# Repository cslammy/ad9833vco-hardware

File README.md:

# ad9833vco-hardware
Schematics, eagle files etc for AD9833 VCO

I have an ongoing project--building a volt octave VCO using the AD9833 function generator IC.  This repo has current zips of Eagle files, BOMs, gerbers, and PDFs of boards and schematics.

What I post here (1-30-23) works on my bench but could stand some improvement in terms of frequency stability and generally improving the triangle to ramp conversion. The rest of it seems to work. I will update the zips here as I continue to improve this design...

Blog post (which links other posts about this project) is here.
https://audiodiwhy.blogspot.com/2023/01/ad9833-audio-vco-works-work-in-progress.html

Embedded C for this project can be found in this repo: AD9833-VCO

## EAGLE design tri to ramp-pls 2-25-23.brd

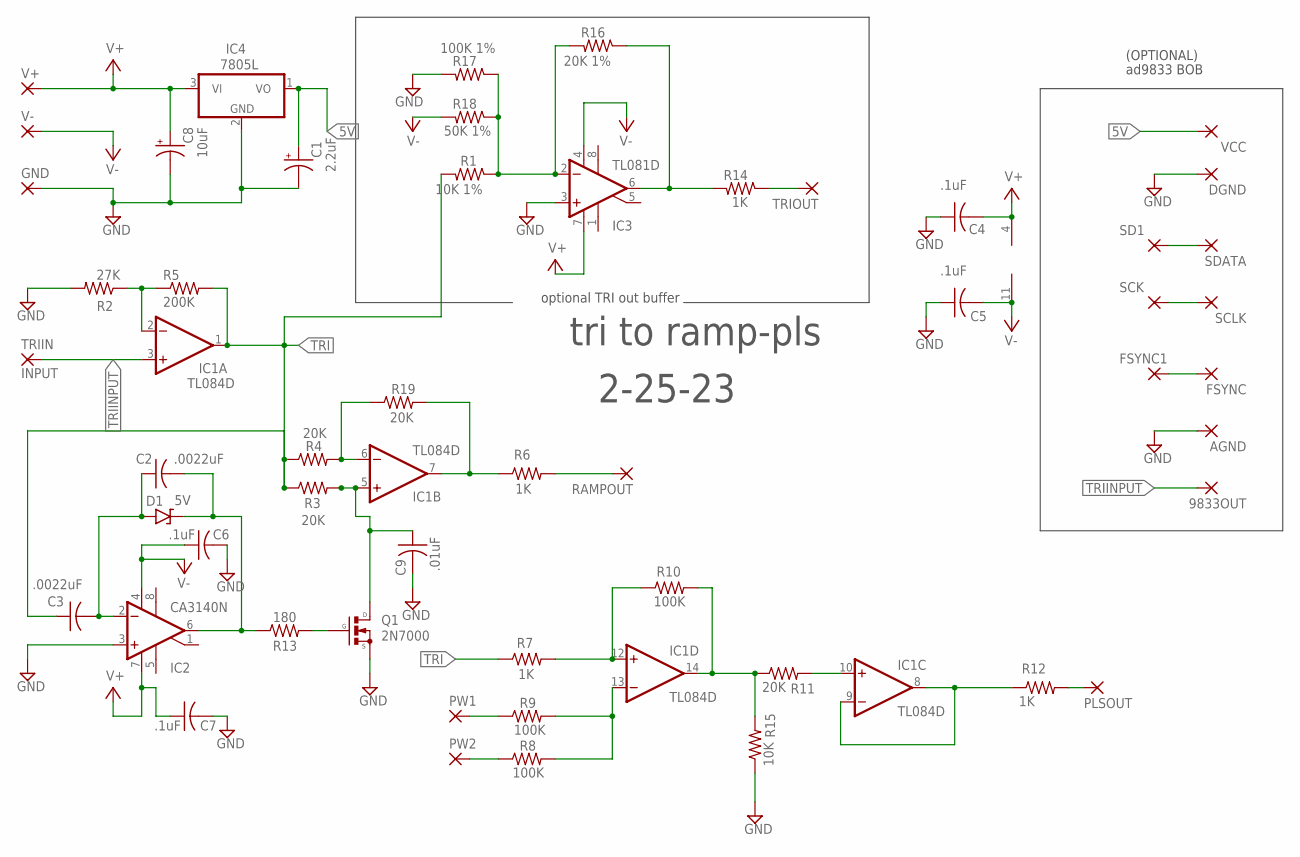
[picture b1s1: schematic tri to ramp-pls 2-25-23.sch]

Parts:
9833OUT: WIREPAD1,6/0,8; 1,6/0,8
AGND: WIREPAD1,6/0,8; 1,6/0,8
C1: 2.2uF; E5-4
C2: .0022uF; C050-030X075
C3: .0022uF; C050-035X075
C4, C5, C6, C7: .1uF; C025-025X050
C8: 10uF; E5-4
C9: .01uF; C050-035X075
D1: 5V; DO41-3
DGND: WIREPAD1,6/0,8; 1,6/0,8
FSYNC, FSYNC1: WIREPAD1,6/0,8; 1,6/0,8
GND: WIREPAD1,6/0,8; 1,6/0,8
IC1: TL084D; SO14
IC2: CA3140N; DIL08
IC3: TL081D; SO08
IC4: 7805L; ADAFRUIT_TO92
PLSOUT: WIREPAD1,6/0,8; 1,6/0,8
PW1, PW2: WIREPAD1,6/0,8; 1,6/0,8
Q1: 2N7000; TO92-
R1: 10K 1%; 0204/7
R2: 27K; 0204/7
R3, R4, R11, R19: 20K; 0204/7
R5: 200K; 0204/7
R6, R7, R12, R14: 1K; 0204/7
R8, R9, R10: 100K; 0204/7
R13: 180; 0204/7
R15: 10K; 0204/7
R16: 20K 1%; 0204/7
R17: 100K 1%; 0204/7
R18: 50K 1%; 0204/7
RAMPOUT: WIREPAD1,6/0,8; 1,6/0,8
SCK: WIREPAD1,6/0,8; 1,6/0,8
SCLK: WIREPAD1,6/0,8; 1,6/0,8
SD1: WIREPAD1,6/0,8; 1,6/0,8
SDATA: WIREPAD1,6/0,8; 1,6/0,8
TRIIN: INPUT; 1,6/0,8
TRIOUT: WIREPAD1,6/0,8; 1,6/0,8
V+: WIREPAD1,6/0,8; 1,6/0,8
V-: WIREPAD1,6/0,8; 1,6/0,8
VCC: WIREPAD1,6/0,8; 1,6/0,8

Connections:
5V: C1.+, IC4.1 (VO), VCC.1
GND: AGND.1, C1.-, C4.1, C5.1, C6.2, C7.2, C8.-, C9.2, DGND.1, GND.1, IC2.3 (+IN), IC3.3 (+IN), IC4.2 (GND), Q1.3 (S), R2.2, R15.1, R17.2
unnamed: IC1.2 (-IN), R2.1, R5.1
unnamed: PW1.1, R9.1
unnamed: SD1.1, SDATA.1
unnamed: IC1.12 (+IN), R7.2, R10.1
unnamed: IC1.6 (-IN), R4.2, R19.1
unnamed: C9.1, IC1.5 (+IN), Q1.1 (D), R3.2
unnamed: C2.1, C3.2, D1.A, IC2.2 (-IN)
unnamed: IC1.7 (OUT), R6.1, R19.2
unnamed: C2.2, D1.C, IC2.6 (OUT), R13.1
unnamed: Q1.2 (G), R13.2
unnamed: IC1.14 (OUT), R10.2, R11.1, R15.2
unnamed: R6.2, RAMPOUT.1
unnamed: IC1.10 (+IN), R11.2
unnamed: IC1.8 (OUT), IC1.9 (-IN), R12.1
unnamed: PLSOUT.1, R12.2
unnamed: IC1.13 (-IN), R8.2, R9.2
unnamed: IC3.2 (-IN), R1.1, R16.2, R17.1, R18.1
unnamed: PW2.1, R8.1
unnamed: R14.1, TRIOUT.1
unnamed: SCK.1, SCLK.1
unnamed: FSYNC.1, FSYNC1.1
unnamed: IC3.6 (OUT), R14.2, R16.1
TRI: C3.1, IC1.1 (OUT), R1.2, R3.1, R4.1, R5.2, R7.1
TRIINPUT: 9833OUT.1, IC1.3 (+IN), TRIIN.1
V+: C4.2, C7.1, C8.+, IC1.4 (V+), IC2.7 (V+), IC3.7 (V+), IC4.3 (VI), V+.1
V-: C5.2, C6.1, IC1.11 (V-), IC2.4 (V-), IC3.4 (V-), R18.2, V-.1

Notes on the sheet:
tri to ramp-pls
2-25-23
optional TRI out buffer
ad9833 BOB
(OPTIONAL)

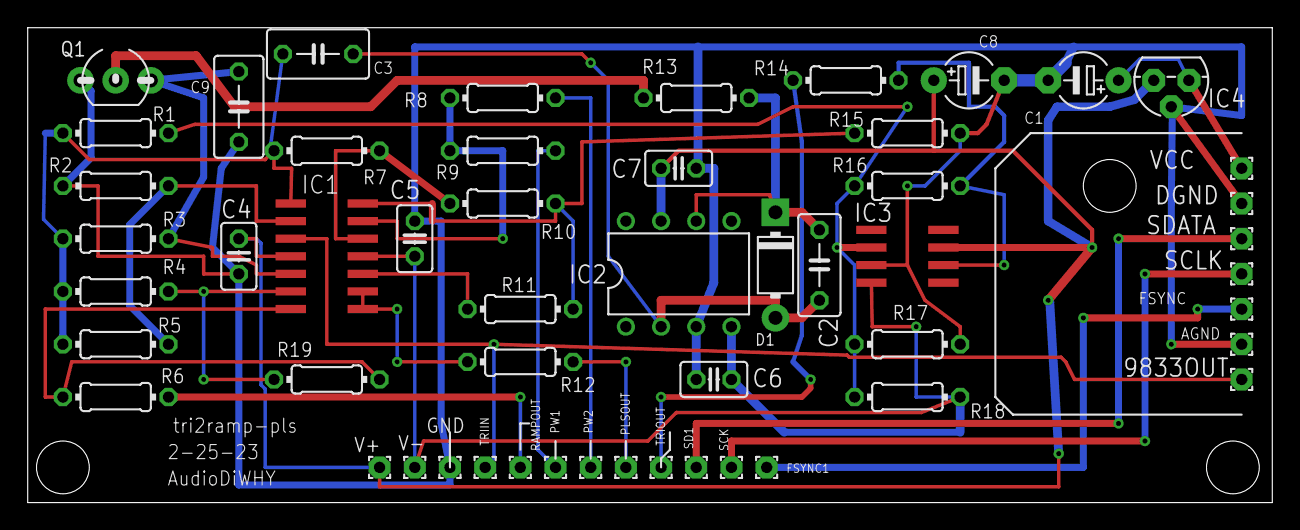
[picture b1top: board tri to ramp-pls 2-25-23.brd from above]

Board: 2 copper layers, 89.8 x 34.3 mm, 53 parts (0 on the bottom side), 28 nets.

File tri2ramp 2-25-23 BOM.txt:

tri to ramp-pls 2-25-23.sch 

Part    Value   Device          Package       Description                          POPULARITY SPICEPREFIX
        1                     
C1      2.2uF   CPOL-USE5-4     E5-4          POLARIZED CAPACITOR, American symbol                       
C2      .0022uF C-US050-030X075 C050-030X075  CAPACITOR, American symbol           5          C          
C3      .0022uF C-US050-035X075 C050-035X075  CAPACITOR, American symbol           0          C          
C4      .1uF    C-US025-025X050 C025-025X050  CAPACITOR, American symbol           0          C          
C5      .1uF    C-US025-025X050 C025-025X050  CAPACITOR, American symbol           0          C          
C6      .1uF    C-US025-025X050 C025-025X050  CAPACITOR, American symbol           0          C          
C7      .1uF    C-US025-025X050 C025-025X050  CAPACITOR, American symbol           0          C          
C8      10uF    CPOL-USE5-4     E5-4          POLARIZED CAPACITOR, American symbol                       
C9      .01uF   C-US050-035X075 C050-035X075  CAPACITOR, American symbol           0          C          
D1      5V      ZENER.3         DO41-3        3V Zener                                                           
                  
IC1     TL084D  TL084D          SO14          OP AMP                               4                     
IC2     CA3140N CA3140N         DIL08         OP AMP                               3                     
IC3     TL081D  TL081D          SO08          OP AMP                                                     
IC4     7805L   ADAFRUIT_7805L  ADAFRUIT_TO92 Positive VOLTAGE REGULATOR                                 
         1                     
Q1      2N7000  2N7000          TO92-         MOSFET                                                          
R1      10K 1%  R-US_0204/7     0204/7        RESISTOR, American symbol                                  
R2      27K     R-US_0204/7     0204/7        RESISTOR, American symbol                                  
R3      20K     R-US_0204/7     0204/7        RESISTOR, American symbol                                  
R4      20K     R-US_0204/7     0204/7        RESISTOR, American symbol                                  
R5      200K    R-US_0204/7     0204/7        RESISTOR, American symbol                                  
R6      1K      R-US_0204/7     0204/7        RESISTOR, American symbol                                  
R7      1K      R-US_0204/7     0204/7        RESISTOR, American symbol                                  
R8      100K    R-US_0204/7     0204/7        RESISTOR, American symbol                                  
R9      100K    R-US_0204/7     0204/7        RESISTOR, American symbol                                  
R10     100K    R-US_0204/7     0204/7        RESISTOR, American symbol                                  
R11     20K     R-US_0204/7     0204/7        RESISTOR, American symbol                                  
R12     1K      R-US_0204/7     0204/7        RESISTOR, American symbol                                  
R13     180     R-US_0204/7     0204/7        RESISTOR, American symbol                                  
R14     1K      R-US_0204/7     0204/7        RESISTOR, American symbol                                  
R15     10K     R-US_0204/7     0204/7        RESISTOR, American symbol                                  
R16     20K 1%  R-US_0204/7     0204/7        RESISTOR, American symbol                                  
R17     100K 1% R-US_0204/7     0204/7        RESISTOR, American symbol                                  
R18     50K 1%  R-US_0204/7     0204/7        RESISTOR, American symbol                                  
R19     20K     R-US_0204/7     0204/7        RESISTOR, American symbol                                  

Breakout Board:
Project requires AD9833 Sig Generator with the following pinout:
VCC
DGND
SDATA
SCLK
FSYNC
AGND
OUT

here is one that works (the one I used)
NOYITO AD9833 Programmable Microprocessor Serial Interface Module Sine Square Wave DDS Signal Generator
https://www.amazon.com/NOYITO-Programmable-Microprocessor-In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
There are many other vendors selling boards just like this on Aliexpress, Ebay etc.
But!! Check to make sure what you buy has the pinout above.

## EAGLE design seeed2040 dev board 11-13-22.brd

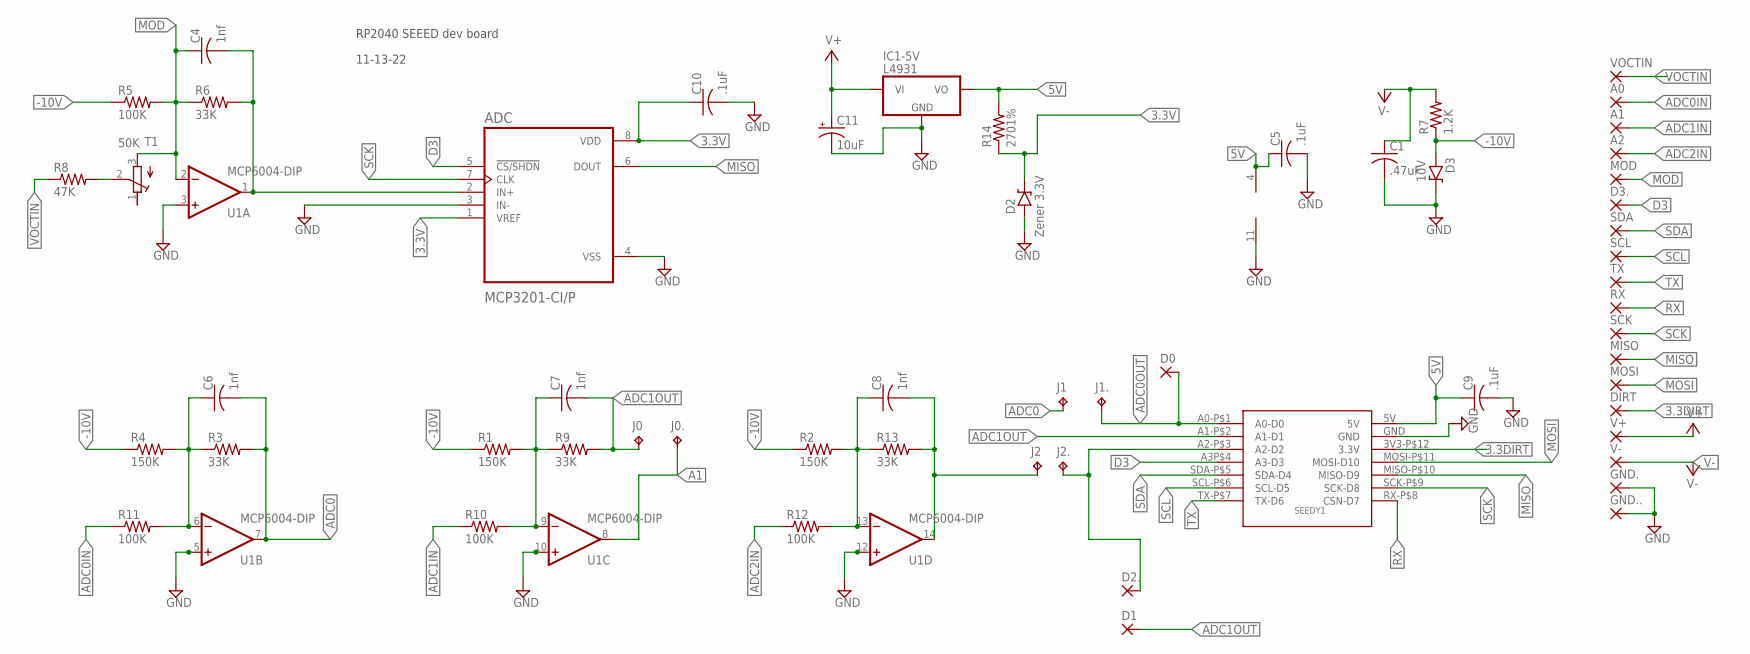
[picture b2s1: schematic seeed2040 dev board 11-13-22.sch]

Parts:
A0, A1, A2: WIREPAD1,6/0,9; 1,6/0,9
ADC: MCP3201-CI/P; DIP787W46P254L927H533Q8
C1: .47uF; C025-030X050
C4, C6, C7, C8: 1nf; C025-025X050
C5, C10: .1uF; C025-025X050
C9: .1uF; C050-025X075
C11: 10uF; E2,5-7
D0, D1, D2., D3.: WIREPAD1,6/0,9; 1,6/0,9
D2: Zener 3.3V; DO41-3
D3: 10V; DO41-3
DIRT: WIREPAD1,6/0,9; 1,6/0,9
GND., GND..: WIREPAD1,6/0,9; 1,6/0,9
IC1-5V: L4931; TO92-
J0, J0., J1, J1., J2, J2.: TPPAD1-13; P1-13
MISO: WIREPAD1,6/0,9; 1,6/0,9
MOD: WIREPAD1,6/0,9; 1,6/0,9
MOSI: WIREPAD1,6/0,9; 1,6/0,9
R1, R2, R4: 150K; 0204/7
R3, R6, R9, R13: 33K; 0204/7
R5, R10, R11, R12: 100K; 0204/7
R7: 1.2K; 0204/7
R8: 47K; 0204/7
R14: 2701%; 0204/7
RX: WIREPAD1,6/0,9; 1,6/0,9
SCK: WIREPAD1,6/0,9; 1,6/0,9
SCL: WIREPAD1,6/0,9; 1,6/0,9
SDA: WIREPAD1,6/0,9; 1,6/0,9
SEEDY1: SEEED_XIAO_RP2040; 14PIN700MIL
T1: 50K; RTRIMT93YA
TX: WIREPAD1,6/0,9; 1,6/0,9
U1: MCP6004-DIP; DIL14
V+: WIREPAD1,6/0,9; 1,6/0,9
V-: WIREPAD1,6/0,9; 1,6/0,9
VOCTIN: WIREPAD1,6/0,9; 1,6/0,9

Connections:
3.3DIRT: DIRT.1, SEEDY1.3V3-P$12 (3.3V)
3.3V: ADC.1 (VREF), ADC.8 (VDD), C10.1, D2.C, R14.1
5V: C5.1, C9.1, IC1-5V.3 (VO), R14.2, SEEDY1.5V, U1.4 (V+)
-10V: D3.A, R1.1, R2.1, R4.1, R5.1, R7.1
A1: J0..TP, U1.8 (OUT)
ADC0: C6.2, J1.TP, R3.2, U1.7 (OUT)
ADC0IN: A0.1, R11.1
ADC0OUT: D0.1, J1..TP, SEEDY1.A0-P$1 (A0-D0)
ADC1IN: A1.1, R10.1
ADC1OUT: C7.2, D1.1, J0.TP, R9.2, SEEDY1.A1-P$2 (A1-D1)
ADC2IN: A2.1, R12.1
ADC2OUT: C8.2, J2.TP, R13.2, U1.14 (OUT)
D3: ADC.5 (!CS/SHDN), D3..1, SEEDY1.A3P$4 (A3-D3)
GND: ADC.3 (IN-), ADC.4 (VSS), C1.2, C5.2, C9.2, C10.2, C11.-, D2.A, D3.C, GND..1, GND...1, IC1-5V.2 (GND), SEEDY1.GND, U1.3 (+IN), U1.5 (+IN), U1.10 (+IN), U1.11 (V-), U1.12 (+IN)
MISO: ADC.6 (DOUT), MISO.1, SEEDY1.MISO-P$10 (MISO-D9)
MOD: C4.1, MOD.1, R5.2, R6.1, T1.3 (A), U1.2 (-IN)
MOSI: MOSI.1, SEEDY1.MOSI-P$11 (MOSI-D10)
unnamed: C6.1, R3.1, R4.2, R11.2, U1.6 (-IN)
unnamed: C7.1, R1.2, R9.1, R10.2, U1.9 (-IN)
unnamed: R8.2, T1.2 (S)
unnamed: C8.1, R2.2, R12.2, R13.1, U1.13 (-IN)
unnamed: D2..1, J2..TP, SEEDY1.A2-P$3 (A2-D2)
RX: RX.1, SEEDY1.RX-P$8 (CSN-D7)
SCK: ADC.7 (CLK), SCK.1, SEEDY1.SCK-P$9 (SCK-D8)
SCL: SCL.1, SEEDY1.SCL-P$6 (SCL-D5)
SDA: SDA.1, SEEDY1.SDA-P$5 (SDA-D4)
TX: SEEDY1.TX-P$7 (TX-D6), TX.1
V+: C11.+, IC1-5V.1 (VI), V+.1
V-: C1.1, R7.2, V-.1
VOCTIN: R8.1, VOCTIN.1
VOCTOUT: ADC.2 (IN+), C4.2, R6.2, U1.1 (OUT)

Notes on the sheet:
RP2040 SEEED dev board
11-13-22

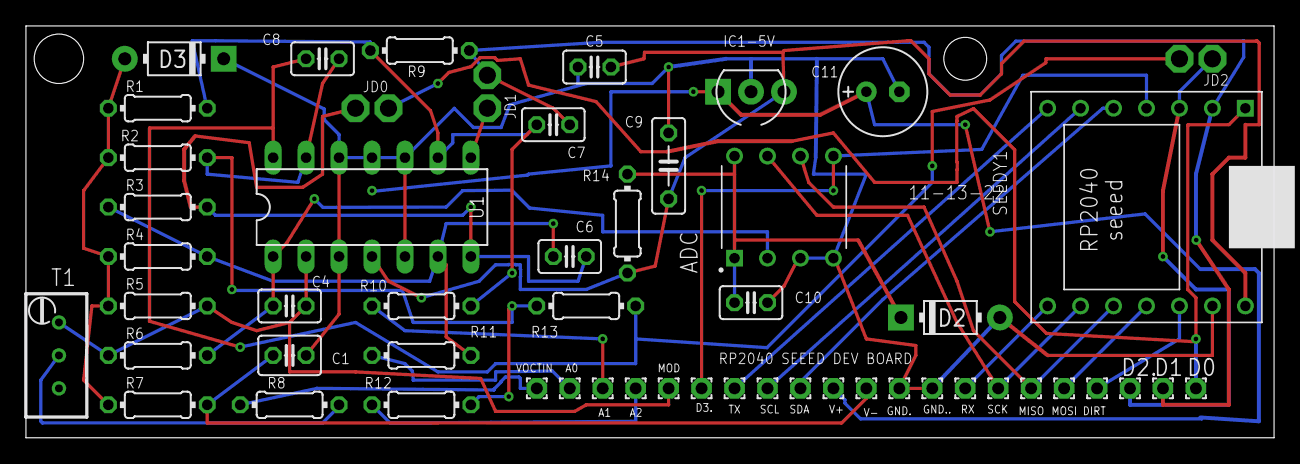
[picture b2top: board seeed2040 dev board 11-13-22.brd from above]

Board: 2 copper layers, 96.2 x 31.7 mm, 57 parts (0 on the bottom side), 31 nets.

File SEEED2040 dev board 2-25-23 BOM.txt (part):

seeed2040 dev board 11-13-22.sch BOM for AD9833 VCO
                                                 
                                                                                                                                                                                                                                                                        
ADC    MCP3201-CI/P      MCP3201-CI/P      DIP787W46P254L927H533Q8    1-Channel Single ADC SAR 100ksps 12-bit Serial Automotive 8-Pin PDIP Tube  Microchip Technology MCP3201-CI/P DIP-8 Microchip                                                               
C1     .47uF             C-US025-030X050   C025-030X050            CAPACITOR, American symbol                                                                                                                                                                                                                                             C                                      
C4     1nf               C-US025-025X050   C025-025X050            CAPACITOR, American symbol                                                                                                                                                                                                                                              C                                      
C5     .1uF              C-US025-025X050   C025-025X050            CAPACITOR, American symbol                                                                                                                                                                                                                                           C                                      
C6     1nf               C-US025-025X050   C025-025X050            CAPACITOR, American symbol                                                                                                                                                                                                                                          C                                      
C7     1nf               C-US025-025X050   C025-025X050            CAPACITOR, American symbol                                                                                                                                                      
C8     1nf               C-US025-025X050   C025-025X050            CAPACITOR, American symbol                                                                                                                                                                                                                                             C                                      
C9     .1uF              C-US050-025X075   C050-025X075            CAPACITOR, American symbol                                                                                                                                                                                                                                                                                       
C10    .1uF              C-US025-025X050   C025-025X050            CAPACITOR, American symbol                                                                                                                                                                                                                                               C                                      
C11    10uF              CPOL-USE2.5-7     E2,5-7                  POLARIZED CAPACITOR, American symbol                                                                                                                                                                                                                                      C                                      
                                                                                                                                                                                                                                                                                 
D2     Zener 3.3V        ZENER.3           DO41-3                   zener diode                                                                                                                                                                                                                                                                                                                
                                                                                                                                                                                                                                                                                 
D3     10V               ZENER.3           DO41-3                   zener diode                                                                                                                                                                                                                                                                                                                
                                                                                                                                                                                                                                                                                 
IC1-5V L4931             L4931             TO92-                    Voltage regulator                                                                                                                                                                                                                                                                                                                
                                                                                                                                                                                                                                                                               
R1     150K**              R-US_0204/7       0204/7                  RESISTOR, American symbol                                                                                                                                                                                                                                                                                        
R2     150K**              R-US_0204/7       0204/7                  RESISTOR, American symbol                                                                                                                                                                                                                                                                                        
R3     33K**               R-US_0204/7       0204/7                  RESISTOR, American symbol                                                                                                                                                                                                                                                                                        
R4     150K**              R-US_0204/7       0204/7                  RESISTOR, American symbol                                                                                                                                                                                                                                                                                        
R5     100K              R-US_0204/7       0204/7                  RESISTOR, American symbol                                                                                                                                                                                                                                                                                        
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
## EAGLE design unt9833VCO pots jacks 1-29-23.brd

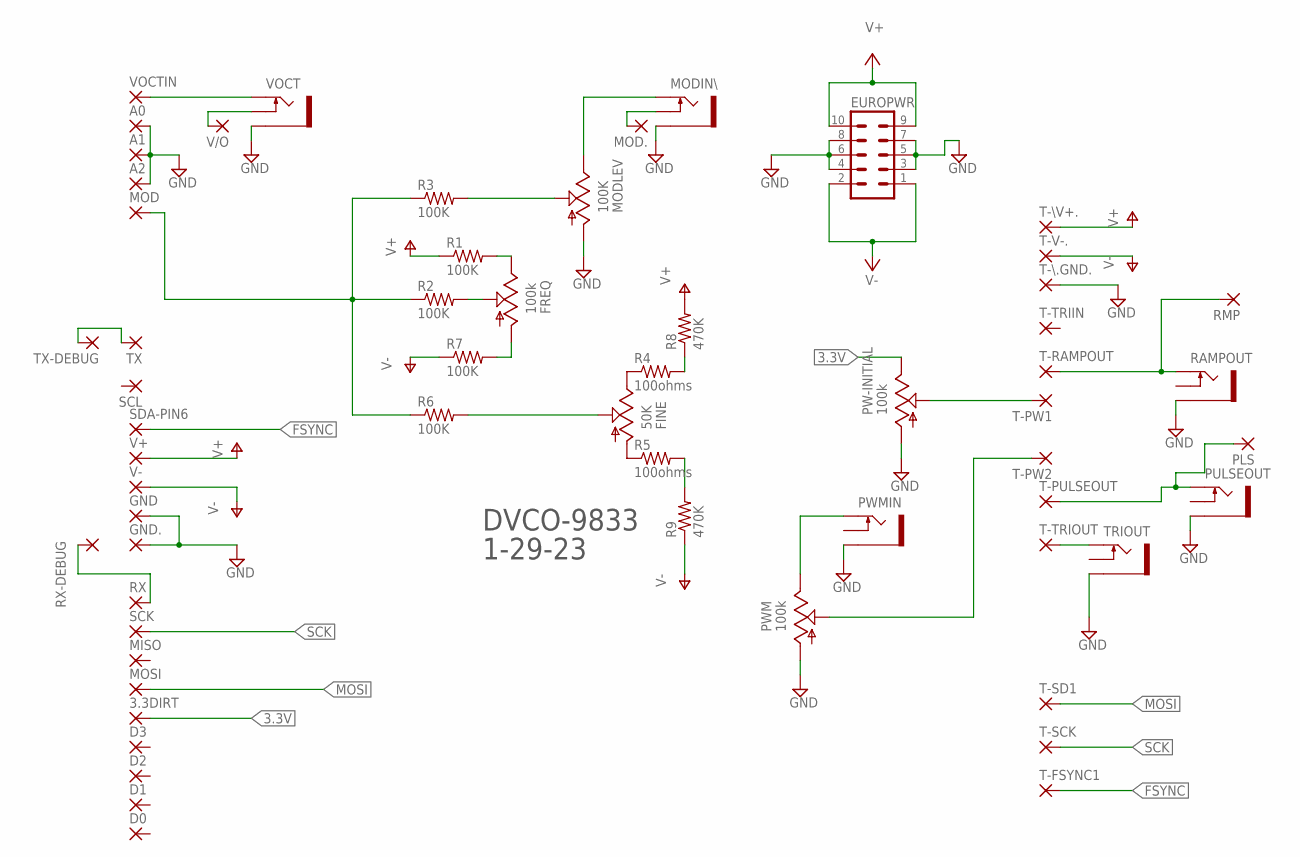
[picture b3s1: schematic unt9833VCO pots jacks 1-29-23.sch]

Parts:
3.3DIRT: WIREPAD1,6/0,9; 1,6/0,9
A0, A1, A2: WIREPAD1,6/0,9; 1,6/0,9
D0, D1, D2, D3: WIREPAD1,6/0,9; 1,6/0,9
EUROPWR: EURO_POWER_HEADERREGULAR; EURO_POWER_HEADER
FINE: 50K; 9MM_SNAP-IN_POT
FREQ: 100k; 9MM_SNAP-IN_POT
GND, GND.: WIREPAD1,6/0,9; 1,6/0,9
MISO: WIREPAD1,6/0,9; 1,6/0,9
MOD, MOD.: WIREPAD1,6/0,9; 1,6/0,9
MODIN\: THONKICONNNEW; WQP-PJ301M-12_JACK
MODLEV: 100K; 9MM_SNAP-IN_POT
MOSI: WIREPAD1,6/0,9; 1,6/0,9
PLS: WIREPAD1,6/0,9; 1,6/0,9
PULSEOUT: THONKICONNNEW; WQP-PJ301M-12_JACK
PW-INITIAL: 100k; 9MM_SNAP-IN_POT
PWM: 100k; 9MM_SNAP-IN_POT
PWMIN: THONKICONNNEW; WQP-PJ301M-12_JACK
R1, R7: 100K; 0204/7
R2, R3, R6: 100K; 0207/15
R4, R5: 100ohms; 0207/15
R8, R9: 470K; 0204/7
RAMPOUT: THONKICONNNEW; WQP-PJ301M-12_JACK
RMP: WIREPAD1,6/0,9; 1,6/0,9
RX: WIREPAD1,6/0,9; 1,6/0,9
RX-DEBUG: WIREPAD1,6/0,9; 1,6/0,9
SCK: WIREPAD1,6/0,9; 1,6/0,9
SCL: WIREPAD1,6/0,9; 1,6/0,9
SDA-PIN6: WIREPAD1,6/0,9; 1,6/0,9
T-FSYNC1: WIREPAD1,6/0,9; 1,6/0,9
T-PULSEOUT: WIREPAD1,6/0,9; 1,6/0,9
T-PW1, T-PW2: WIREPAD1,6/0,9; 1,6/0,9
T-RAMPOUT: WIREPAD1,6/0,9; 1,6/0,9
T-SCK: WIREPAD1,6/0,9; 1,6/0,9
T-SD1: WIREPAD1,6/0,9; 1,6/0,9
T-TRIIN: WIREPAD1,6/0,9; 1,6/0,9
T-TRIOUT: WIREPAD1,6/0,9; 1,6/0,9
T-V-.: WIREPAD1,6/0,9; 1,6/0,9
T-\.GND.: WIREPAD1,6/0,9; 1,6/0,9
T-\V+.: WIREPAD1,6/0,9; 1,6/0,9
TRIOUT: THONKICONNNEW; WQP-PJ301M-12_JACK
TX: WIREPAD1,6/0,9; 1,6/0,9
TX-DEBUG: WIREPAD1,6/0,9; 1,6/0,9
V+: WIREPAD1,6/0,9; 1,6/0,9
V-: WIREPAD1,6/0,9; 1,6/0,9
V/O: WIREPAD1,6/0,9; 1,6/0,9
VOCT: THONKICONNNEW; WQP-PJ301M-12_JACK
VOCTIN: WIREPAD1,6/0,9; 1,6/0,9

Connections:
3.3V: 3.3DIRT.1, PW-INITIAL.3 (E)
FSYNC: SDA-PIN6.1, T-FSYNC1.1
GND: A0.1, A1.1, A2.1, EUROPWR.3, EUROPWR.4, EUROPWR.5, EUROPWR.6, EUROPWR.7, EUROPWR.8, GND.1, GND..1, MODIN\.P$3_SLEEVE (SLEEVE), MODLEV.1 (A), PULSEOUT.P$3_SLEEVE (SLEEVE), PW-INITIAL.1 (A), PWM.1 (A), PWMIN.P$3_SLEEVE (SLEEVE), RAMPOUT.P$3_SLEEVE (SLEEVE), T-\.GND..1, TRIOUT.P$3_SLEEVE (SLEEVE), VOCT.P$3_SLEEVE (SLEEVE)
MOSI: MOSI.1, T-SD1.1
unnamed: VOCT.P$1_TIP (TIP), VOCTIN.1
unnamed: MOD.1, R2.1, R3.1, R6.1
unnamed: MODIN\.P$1_TIP (TIP), MODLEV.3 (E)
unnamed: MOD..1, MODIN\.P$2_SWITCH (SWITCH)
unnamed: MODLEV.2 (S), R3.2
unnamed: FINE.3 (E), R4.1
unnamed: FINE.1 (A), R5.1
unnamed: FINE.2 (S), R6.2
unnamed: FREQ.2 (S), R2.2
unnamed: PLS.1, PULSEOUT.P$1_TIP (TIP), T-PULSEOUT.1
unnamed: T-TRIOUT.1, TRIOUT.P$1_TIP (TIP)
unnamed: FREQ.3 (E), R1.2
unnamed: PW-INITIAL.2 (S), T-PW1.1
unnamed: PWM.2 (S), T-PW2.1
unnamed: PWM.3 (E), PWMIN.P$1_TIP (TIP)
unnamed: V/O.1, VOCT.P$2_SWITCH (SWITCH)
unnamed: TX.1, TX-DEBUG.1
unnamed: FREQ.1 (A), R7.2
unnamed: RX.1, RX-DEBUG.1
unnamed: R5.2, R9.2
unnamed: R4.2, R8.1
RMP>: RAMPOUT.P$1_TIP (TIP), RMP.1, T-RAMPOUT.1
SCK: SCK.1, T-SCK.1
V+: EUROPWR.9, EUROPWR.10, R1.1, R8.2, T-\V+..1, V+.1
V-: EUROPWR.1, EUROPWR.2, R7.1, R9.1, T-V-..1, V-.1

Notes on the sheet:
DVCO-9833
1-29-23

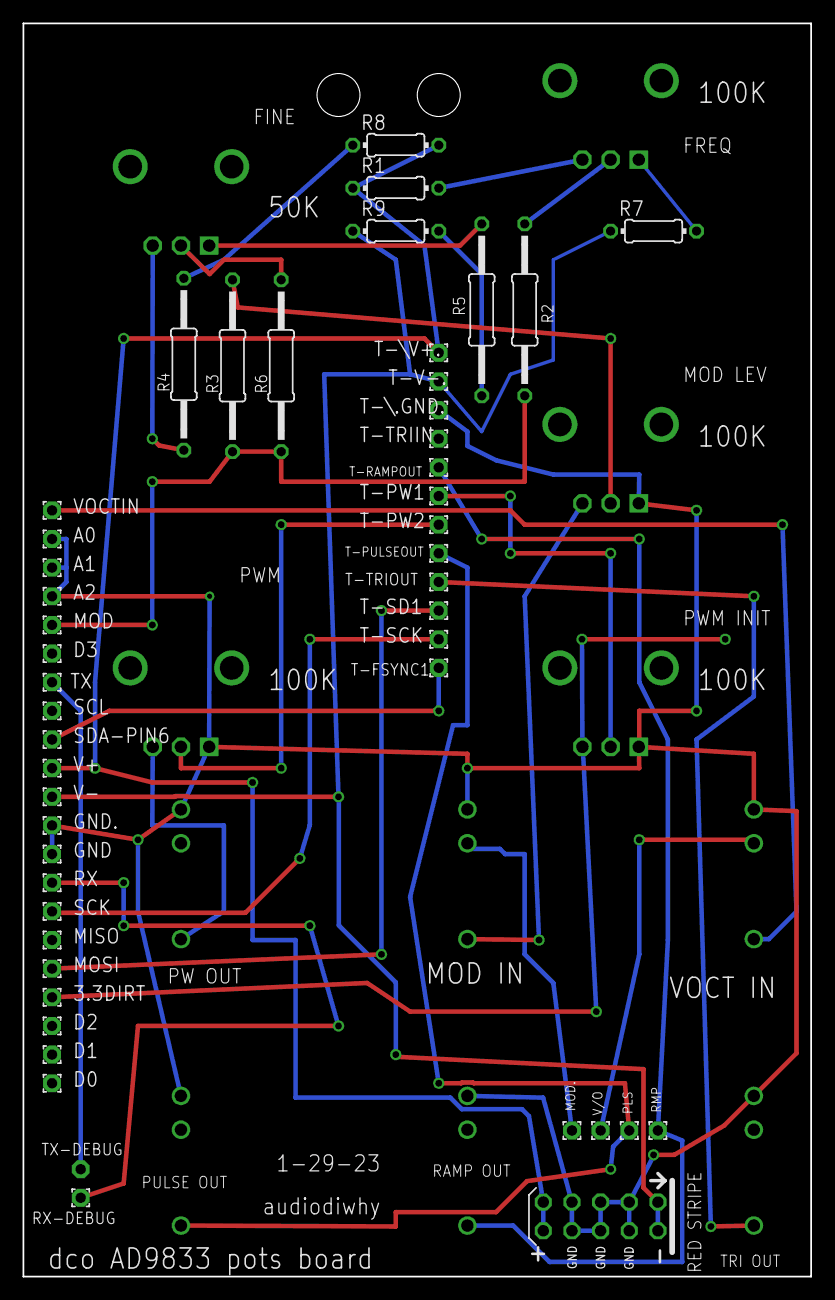
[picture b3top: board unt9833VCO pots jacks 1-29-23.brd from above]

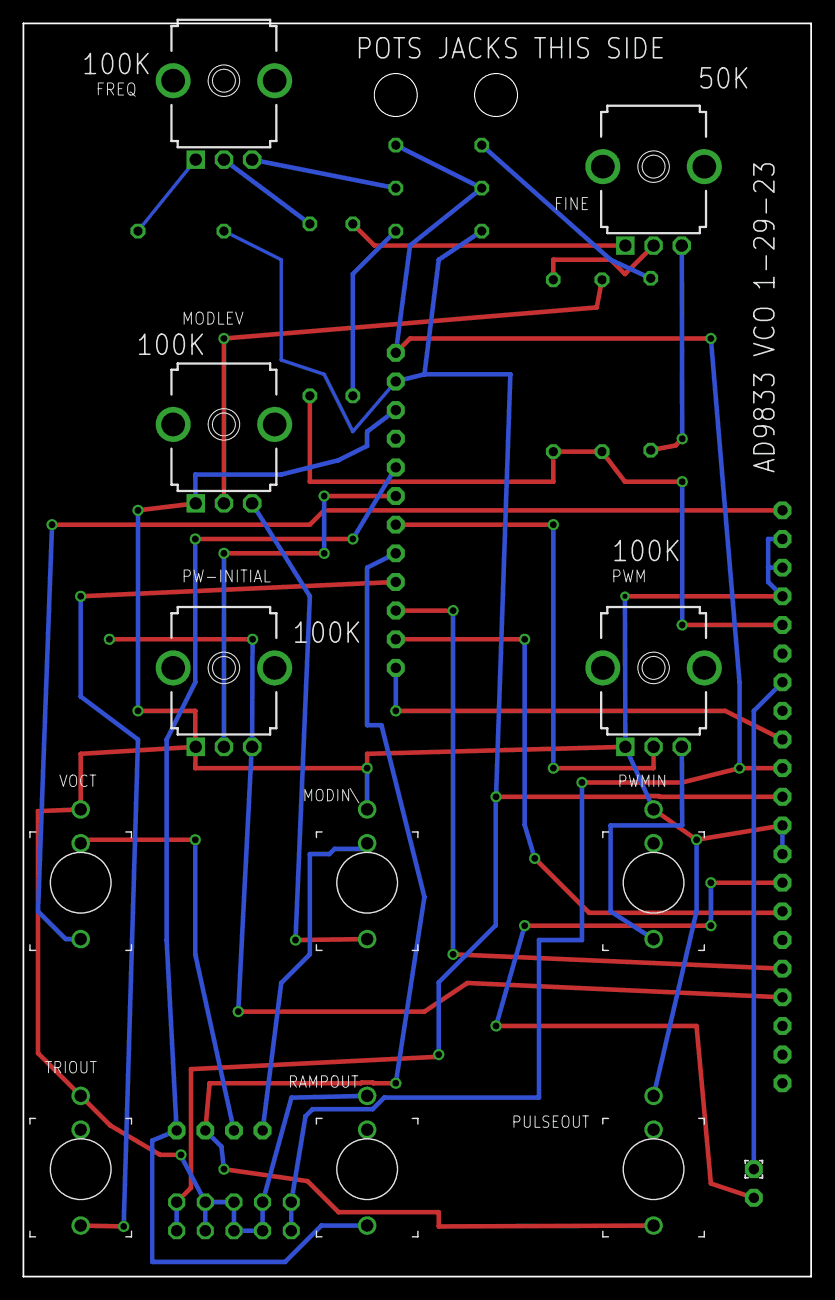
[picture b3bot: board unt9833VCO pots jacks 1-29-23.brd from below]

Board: 2 copper layers, 69.8 x 111.1 mm, 60 parts (12 on the bottom side), 29 nets.

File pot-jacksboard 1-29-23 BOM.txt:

unt9833VCO pots jacks 1-29-23.sch 

Part       Value         Device                   Package            Description                                       POPULARITY SPICEPREFIX
                    
EUROPWR                  EURO_POWER_HEADERREGULAR EURO_POWER_HEADER  Power Header                                                            
FINE       50K           9MM_SNAP-IN_POT_         9MM_SNAP-IN_POT    9mm vertical snap-in pot, Alpha / Panasonic style                       
FREQ       100k          9MM_SNAP-IN_POT_         9MM_SNAP-IN_POT    9mm vertical snap-in pot, Alpha / Panasonic style                       
                     
MODIN\     THONKICONNNEW THONKICONNNEW            WQP-PJ301M-12_JACK 3.5mm socket for Eurorack modular synths                                
MODLEV     100K          9MM_SNAP-IN_POT_         9MM_SNAP-IN_POT    9mm vertical snap-in pot, Alpha / Panasonic style                       
                
PULSEOUT   THONKICONNNEW THONKICONNNEW            WQP-PJ301M-12_JACK 3.5mm socket for Eurorack modular synths                                
PW-INITIAL 100k          9MM_SNAP-IN_POT_         9MM_SNAP-IN_POT    9mm vertical snap-in pot, Alpha / Panasonic style                       
PWM        100k          9MM_SNAP-IN_POT_         9MM_SNAP-IN_POT    9mm vertical snap-in pot, Alpha / Panasonic style                       
PWMIN      THONKICONNNEW THONKICONNNEW            WQP-PJ301M-12_JACK 3.5mm socket for Eurorack modular synths                                
R1         100K          R-US_0204/7              0204/7             RESISTOR, American symbol                         48         R          
R2         100K          R-US_0207/15             0207/15            RESISTOR, American symbol                         0          R          
R3         100K          R-US_0207/15             0207/15            RESISTOR, American symbol                         0          R          
R4         100ohms       R-US_0207/15             0207/15            RESISTOR, American symbol                         0          R          
R5         100ohms       R-US_0207/15             0207/15            RESISTOR, American symbol                         0          R          
R6         100K          R-US_0207/15             0207/15            RESISTOR, American symbol                         0          R          
R7         100K          R-US_0204/7              0204/7             RESISTOR, American symbol                         48         R          
R8         470K          R-US_0204/7              0204/7             RESISTOR, American symbol                         48         R          
R9         470K          R-US_0204/7              0204/7             RESISTOR, American symbol                         48         R          
RAMPOUT    THONKICONNNEW THONKICONNNEW            WQP-PJ301M-12_JACK 3.5mm socket for Eurorack modular synths                                
                    
TRIOUT     THONKICONNNEW THONKICONNNEW            WQP-PJ301M-12_JACK 3.5mm socket for Eurorack modular synths                                
                  
VOCT       THONKICONNNEW THONKICONNNEW            WQP-PJ301M-12_JACK 3.5mm socket for Eurorack modular synths     

For hardware You will need 100mil (2.54mm) male and female PCB edge connectors
Male: Amphenol 	10129378-920003BLF (get 40 pin edge connector and cut apart what you need)
Female: Adafruit 36-PIN 0.1 FEMALE HEADER- 5PK (digikey 1528-2537-ND)

Also 4/40 phillips screws (I used 3/4" Pan Phillips but most anything about this size will work) with nuts and washers to secure daughterboards to this PCB)

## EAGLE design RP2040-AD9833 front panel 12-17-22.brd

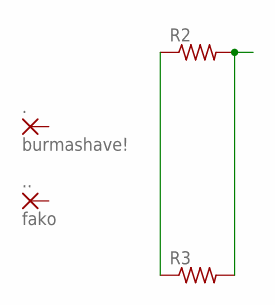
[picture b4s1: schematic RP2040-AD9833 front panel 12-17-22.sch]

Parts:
.: burmashave!; WIREPAD_SMD1,27-2,54
..: fako; WIREPAD_SMD1,27-2,54
R2, R3: R-US_MELF0207R; MINI_MELF-0207R

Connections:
unnamed: R2.1, R3.1
unnamed: R2.2, R3.2

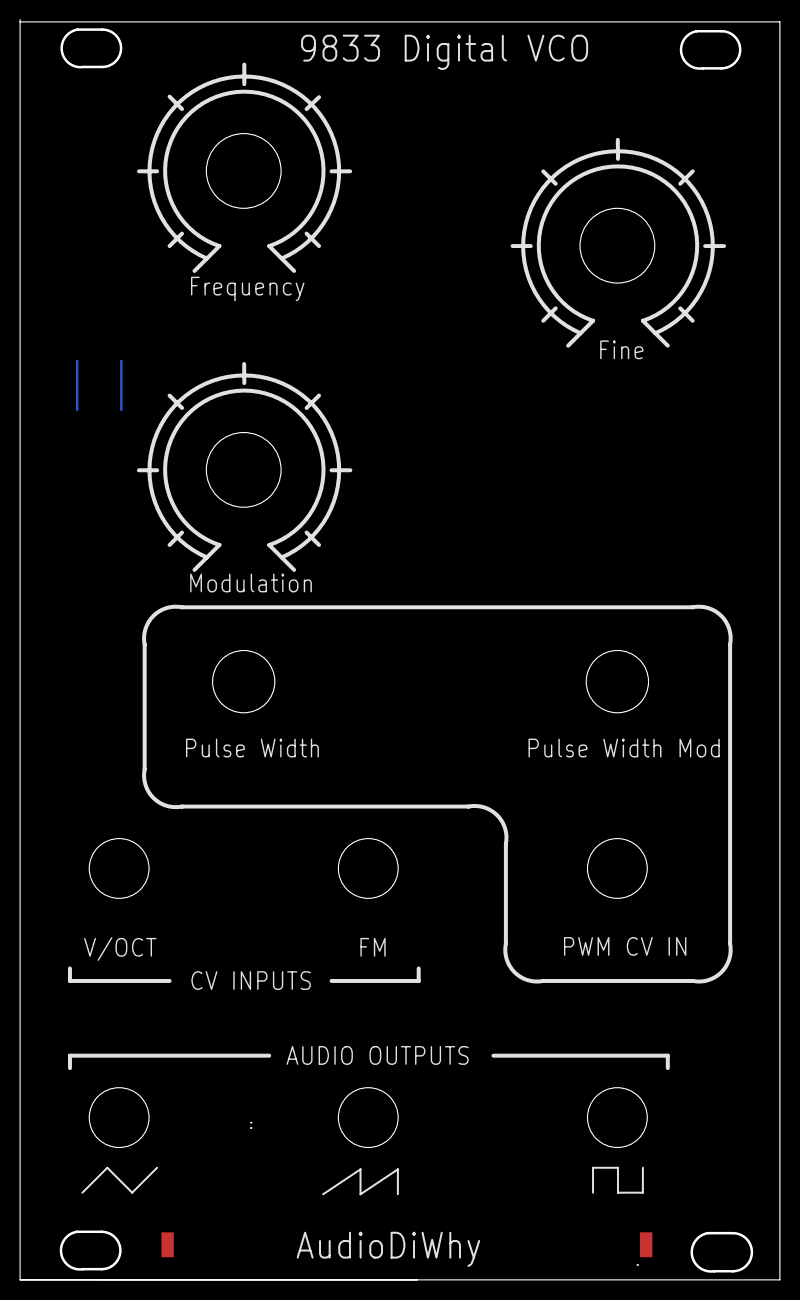
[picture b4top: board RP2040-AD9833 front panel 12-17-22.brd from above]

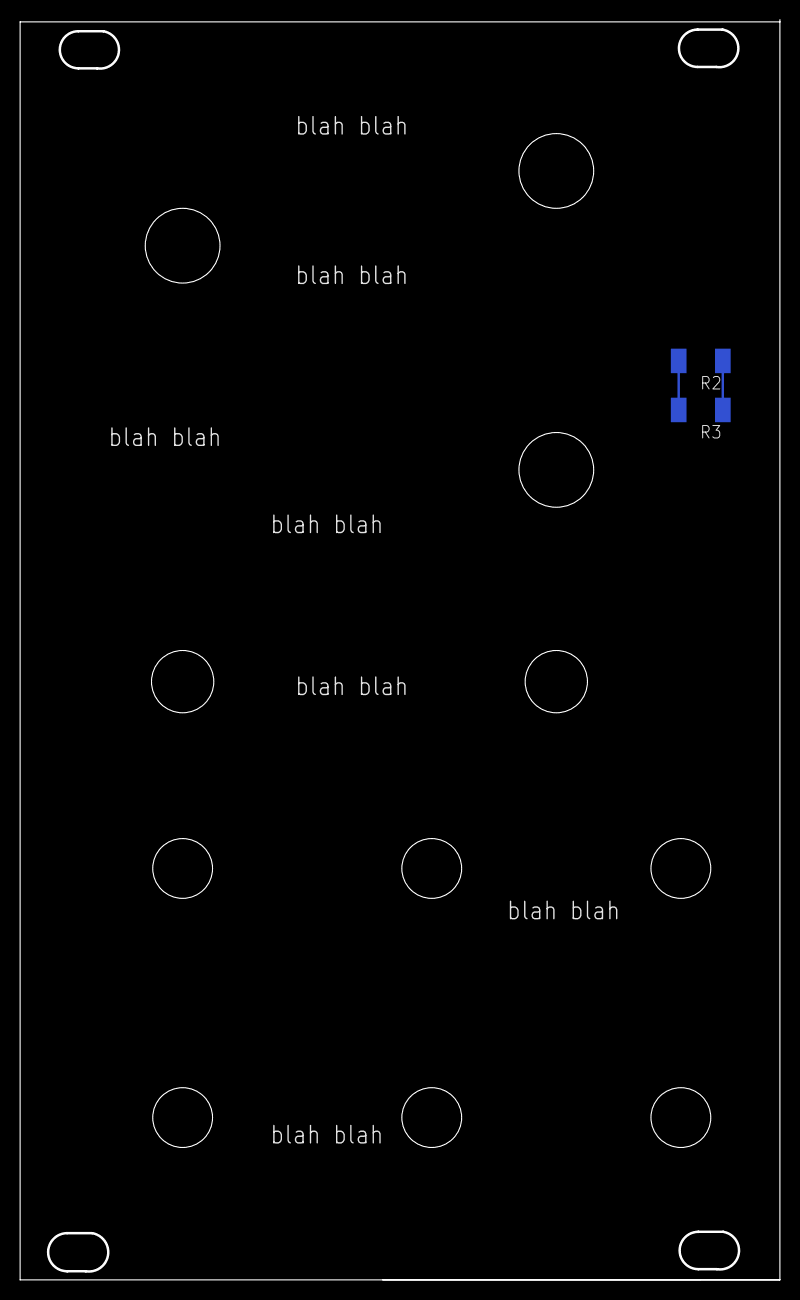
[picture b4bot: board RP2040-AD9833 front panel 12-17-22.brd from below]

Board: 2 copper layers, 77.5 x 128.3 mm, 4 parts (2 on the bottom side), 2 nets.
